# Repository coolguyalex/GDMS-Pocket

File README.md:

# GDMS:Pocket
**Goblinoid Dungeon Mastering System** — microcontroller-based handheld random table roller for tabletop RPGs.

---

## Concept

A dungeon master's companion designed to stay out of the way until you need it. Pull it out, roll a name, an encounter, a room, or whatever your table demands, then put it back in your pocket. GDMS:Pocket is designed to be as ignorable as it is useful — no app, no screen glare, no dead battery notification from your phone mid-session.

Content lives on a microSD card as plain CSV files and JSON recipe files. Adding, removing, or editing tables requires nothing more than a computer and a text editor.

---

## Current Firmware: Alpha 10 

### Implemented Features

- Navigate categories corresponding to folders on the SD card
- Browse and select CSV tables or JSON recipe generators within each category
- Roll a random result with a single button press; re-roll instantly with the same button
- Scroll long results that exceed the screen height
- Hold UP/DOWN for fast scrolling through lists
- LED breathing animation indicates power-on state
- LED "pop" flash on every button press
- Passive buzzer feedback — distinct tones per button
- Full options menu (A+B combo from any screen):
  - Buzzer on/off and volume (loud/soft)
  - LED on/off, pop on/off, brightness (low/med/high)
  - Breath speed (fast/med/slow)
  - Sleep timeout (5 min / 10 min / 30 min / never)
  - Data Edit Mode — exposes the SD card as a USB mass storage drive
- Settings persist to SD card (`/DATA/settings.cfg`) and reload on boot
- Sleep mode: display blanks after inactivity timeout; any button wakes it (suspended while in Data Edit Mode)
- Live battery voltage indicator in the header — 3-bar icon with critical flash
- Header titles truncated with `...` if they would overlap the battery icon
- Startup splash screen (2 seconds on boot)
- About screen with control reference

### Data Edit Mode

Selecting "Data Edit" from the options menu puts the device into USB mass storage mode: the SD card mounts on the connected computer as a normal removable drive, so content can be added, edited, or removed with a regular file explorer — no card removal required. The device still charges normally over the same USB-C connection while in this mode.

- Entered from the options menu (A → cycles into the mode)
- Screen displays "DATA EDIT MODE" / "press A + B to exit." while active
- Exit via A+B (held) — the same combo used elsewhere to open the options menu is repurposed here to exit, since the options menu isn't reachable while the SD card is handed off to the host
- On exit, the SD card is unmounted from the host, remounted for the firmware's own file access, and categories are rescanned so any added/removed/edited content shows up immediately
- Implemented via Adafruit_TinyUSB's mass storage (MSC) class, using the same SdFat `SD` object already used for file-level access elsewhere in the firmware — read/write/flush callbacks operate at the raw sector level rather than the file level
- Sleep timeout is disabled while in this mode so the screen doesn't blank mid-transfer

### JSON Recipe System (V1)

JSON files in a category folder act as multi-part generators. A recipe chains together rolls from multiple CSV tables and assembles them into a single composed output. Features include optional parts (probability `p`), repeat counts, cross-category table references, and a `format` string for custom output layouts. See **Content & Customisation** below and the recipe convention document in the repo for full details.

### CSV Weighted Tables

If a CSV file uses two columns — `weight,entry` — the first column is treated as an integer weight and results are sampled proportionally. Single-column CSVs treat all entries as equally likely. Lines beginning with `#` or `//` are treated as comments and skipped.

---

## Hardware

### Bill of Materials

| Component | Description |
|-----------|-------------|
| Adafruit Feather RP2040 Adalogger | MCU + built-in microSD slot |
| 1.5" SH1107 OLED (SPI, 128×128) | Display |
| 4× momentary pushbutton | Navigation (active-low) |
| Passive buzzer module (3-pin) | Audio feedback |
| LED + current-limiting resistor | Status indicator |
| 3.7V LiPo battery (JST connector) | Power |
| 2× 100kΩ resistor | Battery voltage divider |

### BOM with cost estimates
|Component                                |Price     |Source                                |
|-----------------------------------------|----------|--------------------------------------|
|Adafruit Feather RP2040 Adalogger        |$14.95    |Adafruit / DigiKey, retail single unit|
|1.5” SH1107 128×128 monochrome OLED (SPI)|$4.50     |AliExpress, bulk 10-pack pricing      |
|Momentary pushbuttons ×4                 |$0.60     |AliExpress, bulk 100pc pack           |
|Passive buzzer module                    |$0.35     |AliExpress, bulk pack                 |
|LED + resistor                           |$0.10     |AliExpress, bulk pack                 |
|3.7V LiPo battery w/ JST                 |$2.50     |AliExpress, bulk pack                 |
|100kΩ resistors ×2                       |$0.02     |AliExpress, bulk reel                 |
|Slide switch                             |$0.30     |AliExpress, bulk pack                 |
|Custom PCB, bare board (10-unit batch)   |$1.50     |PCBWay                                |
|3D printed PETG enclosure                |$3.00     |Self-sourced filament                 |
|Misc wire/headers/hardware               |$1.00     |AliExpress, bulk pack                 |
|**Total**                                |**$28.82**|                                      |

### Pin Mapping

#### OLED Display (SH1107, Software SPI)

| OLED Pin | Feather Pin |
|----------|-------------|
| VCC | 3V3 |
| GND | GND |
| SCL (CLK) | D13 |
| SDA (DATA) | D12 |
| DC | D11 |
| CS | D10 |
| RST | D9 |

> **Library patch required:** The U8g2 SH1107 128×128 driver sets `default_x_offset = 96` by default, which causes a 32px horizontal wrap on some panels. Set both `default_x_offset` and `flipmode_x_offset` to `0` in `u8x8_d_sh1107.c`. This must be re-applied after any U8g2 library update. See Log 8 for full details.
>
> This has recurred at least once in practice after installing an unrelated library (Adafruit TinyUSB) via Library Manager, which appears to have triggered a U8g2 reinstall/update as a side effect. Worth checking `default_x_offset`/`flipmode_x_offset` any time the display shows an unexplained horizontal shift, not just after deliberate U8g2 updates. As of U8g2's source (checked Feb 2025), the maintainer's own comment on this section confirms `0` is the correct value for panels like this one — see [olikraus/u8g2#2581](https://github.com/olikraus/u8g2/issues/2581).

#### Buttons (Active-Low, Internal Pull-Up)

| Button | Feather Pin |
|--------|-------------|
| UP | A1 |
| DOWN | A2 |
| A (select / roll) | A3 |
| B (back) | 24 |

Buttons are wired pin → GND. No external pull-up resistors needed.

#### Buzzer (Passive, PWM)

| Signal | Feather Pin |
|--------|-------------|
| SIG | D6 |
| VCC | 3V3 |
| GND | GND |

> A series resistor (~1kΩ) on the signal line is recommended to reduce volume to a comfortable level for table use.

#### LED

| Connection | Feather Pin |
|------------|-------------|
| Anode (via resistor) | D25 |
| Cathode | GND |

> Do not use `PIN_LED` as a variable name — it is defined as a macro in the RP2040 Arduino core.

#### Battery Voltage Divider

The Feather RP2040 Adalogger does not have a built-in battery monitor circuit. An external voltage divider must be wired as follows:

```
VBAT ──[ 100kΩ ]──┬──[ 100kΩ ]── GND
                  │
                  └── A0
```

| Signal | Feather Pin |
|--------|-------------|
| Divider center tap | A0 |

The firmware reads A0, multiplies by 2, and displays a 3-bar battery icon in the header. Voltage thresholds: FULL ≥4.0V, OK ≥3.7V, LOW ≥3.5V, CRIT <3.5V (flashing).

### SD Card

The Adalogger's built-in microSD slot is used via SdFat (Adafruit fork) on SPI1. Format the card as FAT32.

---

## SD Card Data Structure

```
/DATA/
  /category-name/
    table.csv
    generator.json
    _hidden-ingredient.csv
  /another-category/
    ...
  settings.cfg          ← written automatically by firmware
```

- `/DATA` is the root content directory. It must exist.
- Each immediate subfolder of `/DATA` becomes a navigable category in the UI.
- Folders nested deeper than one level are ignored.
- `.csv` and `.json` files within a category folder appear as selectable items.
- Files whose names begin with `_` are hidden from the UI but accessible to JSON recipes.
- `settings.cfg` is written automatically and should not be edited manually.

---

## Software

### Language & Framework

Arduino (C++) targeting the Adafruit Feather RP2040 Adalogger via the Arduino-Pico core.

### Library Dependencies

| Library | Purpose |
|---------|---------|
| U8g2 (olikraus) | OLED driver and graphics |
| SdFat – Adafruit Fork | microSD access |
| ArduinoJson | JSON recipe parsing |
| Adafruit TinyUSB | USB mass storage (Data Edit Mode) — requires Tools > USB Stack > Adafruit TinyUSB in Arduino IDE |

### Controls Reference

| Button | Category / File list | Table / Result view | Options menu | Data Edit Mode |
|--------|---------------------|---------------------|--------------|-----------------|
| UP | Scroll up | Scroll up | Previous option | — |
| DOWN | Scroll down | Scroll down | Next option | — |
| A | Select / enter | Re-roll | Cycle setting value | — |
| B | — (no-op at root) | Back to file list | Back | — |
| A + B (held) | Open options | Open options | — | Exit Data Edit Mode |

### Architecture Notes

- State machine with six modes: `MODE_CATS`, `MODE_FILES`, `MODE_TABLE`, `MODE_OPTIONS`, `MODE_ABOUT`, `MODE_DATA_EDIT`
- Page-buffer OLED rendering (`_1_` constructor) — redraws on input events only, with a periodic background refresh for animation (LED breath, battery icon flash)
- Non-blocking LED and buzzer using `millis()` timers throughout
- Battery sampled every 5 seconds via a non-blocking timer; 8-sample average
- All user settings persisted to `/DATA/settings.cfg` as key=value text immediately on change
- SD card is accessed two ways depending on mode: file-level (`SD.open()`, `FsFile`) for normal category/table browsing, and raw block/sector-level (`SD.card()->readSector()`/`writeSector()`) for Data Edit Mode's USB mass storage exposure — same underlying SdFat object, different API surface

---

## Planned / Future Features

- Auto-mode: a dearf-fortressian ambient atory generatir where randomyl generated entires drive a strange atory which unfolds before the reader. 
- Per-category icons (`_icon.bin`, 32×32 1-bit bitmap) rendered in the header
- Saved results — up to 10 entries written to SD, browsable on a Saved page
- Nested JSON recipes (recipes invoking other recipes)
- Ambient mode — auto-rolls at a set interval for generative table atmosphere
- Neopixel indicator
- Battery voltage shown in the About screen
- Migration from `StaticJsonDocument` to `JsonDocument` (ArduinoJson v7 alignment)
- **GDMS-pocket Companion App** — desktop tool for content authoring, generation, and firmware flashing (see below)

---

## GDMS-pocket Companion App (Planned)

A desktop companion tool for authoring and managing GDMS:Pocket content, shipped alongside the device rather than as a separate purchase. Not yet implemented — this section documents the intended design and open questions.

### Concept

**Data Edit Mode is now implemented on-device** (see Current Firmware above) — the SD card can be exposed as a plain USB mass storage drive from the options menu, no companion app required. The companion app remains planned as a richer, GDMS-aware layer on top of this: same name family, same visual language, same spirit of staying out of the way until needed, but with content-authoring tools (Markov-chain generation, structured CSV/JSON editing, firmware flashing) that a generic file explorer can't offer.

### Aesthetic

Black-on-green CLI-style interface, matching the terminal look of the original [GDMS](https://github.com/coolguyalex/GDMS) desktop tool. Navigation is entirely text-based:
- Keyboard shortcuts for every applet/action
- Clickable text labels as the mouse-driven alternative — text glows on hover and blinks briefly when clicked, echoing a terminal cursor rather than a conventional button

### Device Detection & Interaction

Still an open design question — rough intent:
- When the app is running and a GDMS:Pocket is connected via USB, the device should detect the companion app's presence (likely via a simple serial handshake) and unlock companion-aware functionality on-device, going beyond the generic mass-storage exposure Data Edit Mode already provides.
- Once connected, the app could:
  - Browse and directly edit category folders, CSV tables, and JSON recipes on the SD card
  - Generate new content — e.g. Markov-chain-based text generators trained on existing tables, to bootstrap new CSV entries from a sample of existing ones
  - Flash new firmware to the device (bundling firmware updates with the same tool used for content, instead of requiring separate Arduino IDE / bootloader steps)
  - **Chiptune mode** (low priority / just for fun) — compose or import chiptune-style songs and play them back through the device's passive buzzer, in the spirit of [goblinoidDungeonSynthSystem](https://github.com/coolguyalex/goblinoidDungeonSynthSystem)

### Open Questions

- ~~Whether "Data Edit Mode" on the device becomes a distinct on-device mode of its own, or stays implicit~~ — resolved: it's a distinct on-device mode, entered/exited explicitly from the options menu, and works as plain mass storage independent of any companion app
- Whether the companion app's smarter feature set (content generation, firmware flashing) talks to the device over serial while Data Edit Mode's plain mass-storage exposure remains the fallback for basic editing
- How much of the companion-aware logic should live in GDMS:Pocket firmware itself (e.g. a lightweight serial command protocol) vs. entirely in the companion app

---

## Changelog

| Version | Summary |
|---------|---------|
| Alpha 10| Data Edit Mode (USB mass storage for SD card content editing) |
| Alpha 9 | Battery voltage icon in header, header truncation, stale pin comment fixed |
| Alpha 8 | Scrollbar on category list, additional LED options |
| Alpha 7 | Sleep/wake, scrollbar in table view, About screen in options |
| Alpha 6 | A+B combo options menu |
| Alpha 5 | LED breathing and pop animations |
| Alpha 4 | List scrolling |
| Alpha 3 | Hold-to-scroll on UP/DOWN |
| Alpha 2 | Word-aware line wrapping |
| Alpha 1 | Initial SH1107 bring-up, pin map, full hardware test |

---

*GDMS:Pocket by Alexander Sousa, 2026*

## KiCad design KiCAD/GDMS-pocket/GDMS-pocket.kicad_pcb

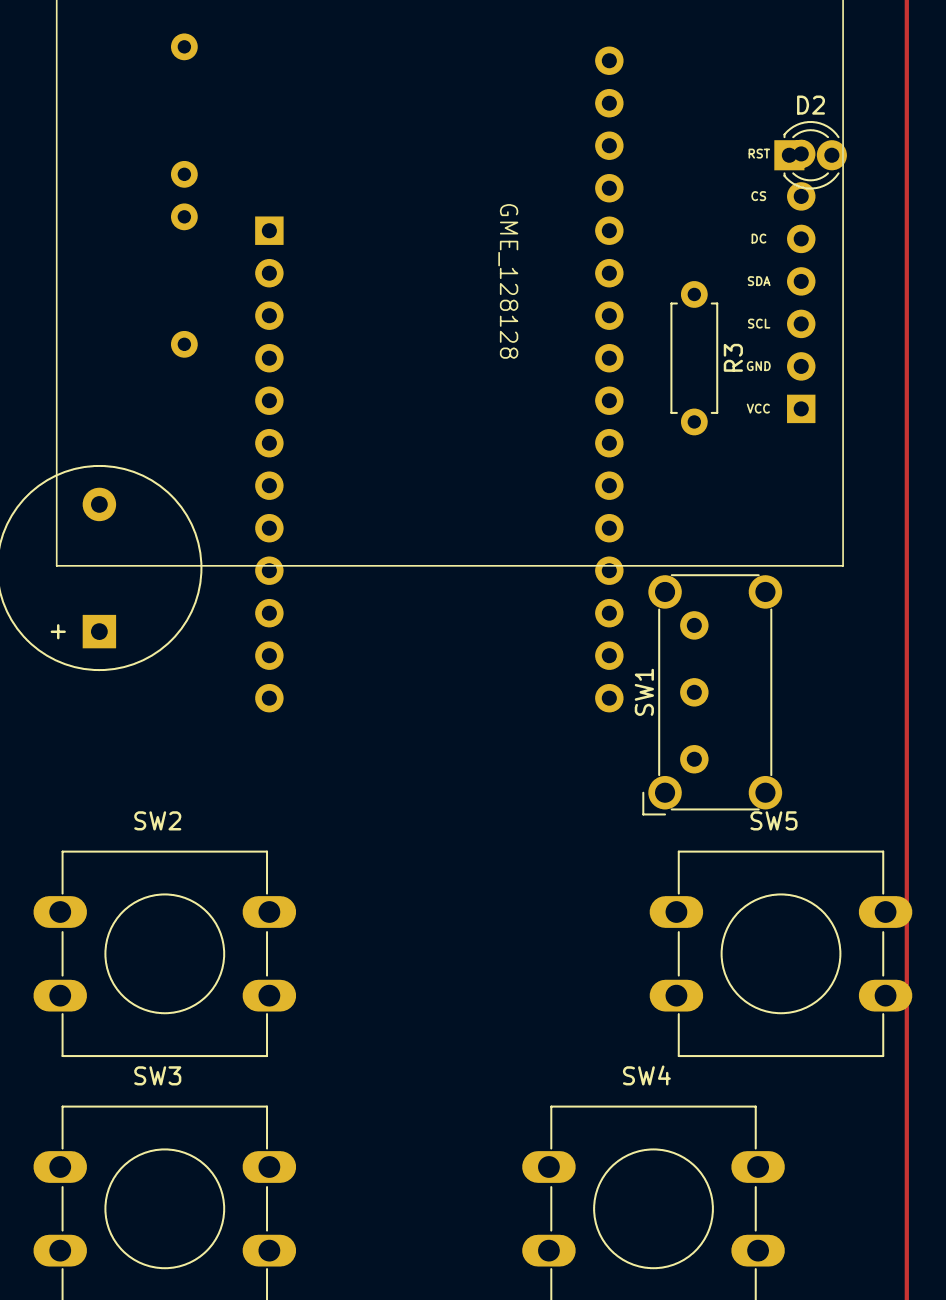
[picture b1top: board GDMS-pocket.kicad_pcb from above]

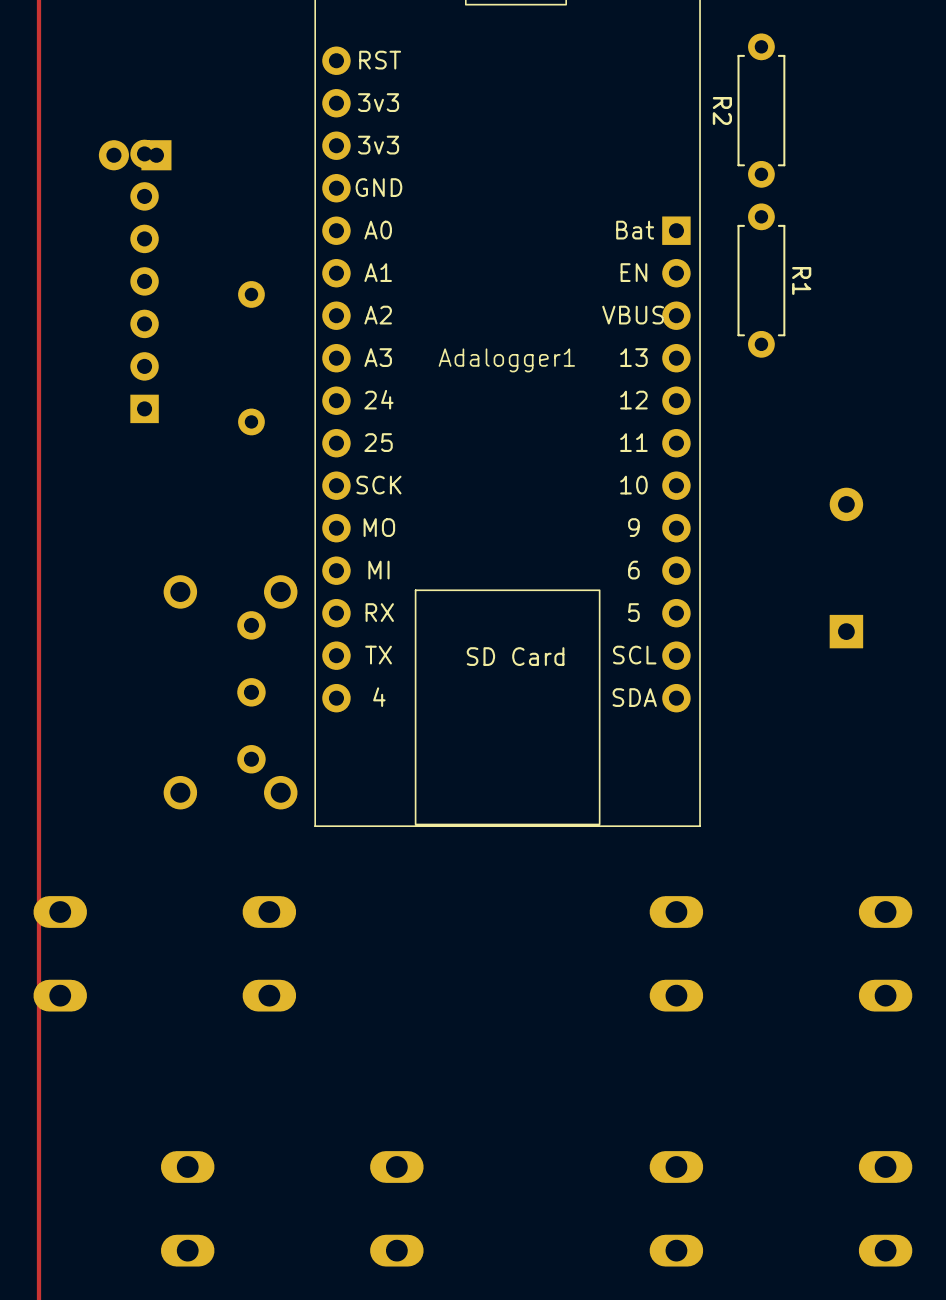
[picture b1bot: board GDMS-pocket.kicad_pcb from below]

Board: 2 copper layers, 12 parts (3 on the bottom side), 17 nets, no tracks yet.

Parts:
Adalogger1: Adafruit Feather Adalogger RP2040; Adafruit_Feather_Adalogger_RP2040
BZ1: Buzzer; Buzzer_12x9.5RM7.6
D2: LED; LED_D3.0mm
GME_128128: SH1107; 128128_SPI_SH1107
R1, R2: 100k; R_Axial_DIN0207_L6.3mm_D2.5mm_P7.62mm_Horizontal
R3: 1k; R_Axial_DIN0207_L6.3mm_D2.5mm_P7.62mm_Horizontal
SW1: SW_SPDT; SW_E-Switch_EG1224_SPDT_Angled
SW2, SW3, SW4, SW5: SW_Push; SW_PUSH-12mm

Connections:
+3V3: Adalogger1.27 (3v3), GME_128128.1 (VCC)
GND: Adalogger1.25 (GND/GND), BZ1.2 (-), D2.1 (K), GME_128128.2 (GND), R2.1, SW1.3 (C), SW2.2, SW3.2, SW4.2, SW5.2
unnamed: Adalogger1.24 (A0/GPIO26), R1.1, R2.2
unnamed: Adalogger1.23 (A1/GPIO27), SW3.1
unnamed: Adalogger1.22 (A2/GPIO28), SW2.1
unnamed: Adalogger1.21 (A3/GPIO29), SW5.1
unnamed: Adalogger1.4 (D6/GPIO6), R3.1
unnamed: Adalogger1.5 (D9/GPIO9), GME_128128.7 (RST)
unnamed: Adalogger1.6 (D10/GPIO10), GME_128128.6 (CS)
unnamed: Adalogger1.7 (D11/GPIO11), GME_128128.5 (DC)
unnamed: Adalogger1.8 (D12/GPIO12), GME_128128.4 (SDA)
unnamed: Adalogger1.9 (D13/GPIO13), GME_128128.3 (SCL)
unnamed: Adalogger1.20 (D24/GPIO24), SW4.1
unnamed: Adalogger1.19 (D25/GPIO25), BZ1.1 (+)
unnamed: Adalogger1.11 (EN), SW1.2 (B)
unnamed: Adalogger1.12 (VBAT), R1.2
unnamed: D2.2 (A), R3.2

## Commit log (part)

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2025-12-25 adding data files
2025-12-25 upload more data and resructure
2025-12-25 new files and rearranged structure
2025-12-25 dice data
2025-12-25 rename and file extension changes
2025-12-26 update files
2025-12-26 file tree screenshot
2025-12-26 file structure
2025-12-26 comment
2025-12-26 changeing files
2025-12-26 reupload
2025-12-26 more readme and file names
2025-12-26 restructure
2025-12-27 updated logs
2025-12-27 stuff
2025-12-27 fixed inaccurate V02 code
2025-12-27 new LED features
    breathing and pop on press
2025-12-28 move sketch
2025-12-28 mini-dice roller for arduino nano
    Sketch design for the nano paying heed to limitted storage and RAM
2025-12-29 writing for arduino nano
    Much code writen for the arduino nano such that an external SD module is not needed. Spartan UI redesign, and other flash memeory and RAM saving measures taken. No SD card means all lists for random 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
    Log updated to reflect changes.
2025-12-29 Rename files, add MCU comparison
2025-12-29 blueprint
2025-12-29 creating tiny-dungeon
2025-12-29 change file ext.
2026-01-02 beginning CircuitPython
2026-01-03 libraries
2026-01-03 example python stuff
2026-01-04 Revise README for GDMS:Pocket with new features
    Updated the README with new features, hardware details, and functionality for GDMS:Pocket.
2026-01-04 MCU boards comparisons
2026-01-04 editting readme to reflect wiring changes
2026-01-04 rearrangign files and folders. adding some test code for V4
2026-01-04 bunch of stuff
2026-01-04 addded a little helper script for batchquoting
2026-01-04 reached POC v1
2026-01-04 final sketch for the night, updated logs, juggled files
2026-01-04 deleted duplicate files
2026-01-06 deleted corrupted version of POC_4
    deleted corrupted version of POC_4 and changed
    #include "SdFat.h"
    to
    #include <SdFat.h>
2026-01-06 Implement SD config file and rearrange files
    Implement SD config file
    rearrange files
    creating plaintext duplicates of code.
2026-01-06 A and B button flip
2026-01-07 Seem to have implemented Adafruit-fork-free SD reading.
2026-01-07 Implemented JSON recipe v1
    JSON Recipe System – V1 Summary
    What V1 Accomplishes
    V1 introduces JSON-based generators (“recipes”) that behave exactly like CSV tables from the user’s point of view, while allowing internally chained rolls.
    Key capabilities:
    JSON recipes appear in the UI alongside CSV tables
    .json files are listed and selectable just like .csv
2026-01-07 Updated to remove deprecated functions
    deprecated arduino Json functions (dynamic vs static) eliminate din favor of newer functions.
2026-01-08 Create delete.txt.
2026-01-08 monster table uploads
2026-01-10 Add OLED test sketch for RP2040 using U8g2 library
2026-01-10 Rename OLED test file to correct format
2026-01-10 Rename delete.txt. to delete.txt
2026-01-10 Revise README for clarity and additional details
    Updated README to enhance clarity and structure, including hardware pin plan, library table, and functional specifications.
2026-01-10 Revise README with project overview and hardware info
    Updated README.md with new project details and hardware specifications.
2026-01-11 Revise README with hardware and software updates
    Updated README to include new hardware details and functionality.
2026-01-11 Revise README for improved structure and content
    Updated README.md to enhance clarity and add details.
2026-01-11 Add dev log for SH1107 OLED bring-up and validation
    Documented the bring-up process and issues encountered with the SH1107 OLED display on the Feather RP2040 Adalogger.
2026-01-11 Rename Log 7 260103 GDMS_Pocket_POC_V03.md to Log7 260103 GDMS_Pocket_POC_V03.md
2026-01-11 better test which includes all components - and renamed
    sketch tests 1.5" 128 x 128 OLED, 4 buttons, passive buzzer, and LED.
2026-01-11 Added JSON Recipes, and SplashScreen
2026-01-11 Enhance development log with JSON recipe details
    Updated the development log to include JSON recipe functions and file ignore behavior.
2026-01-11 Rearranged files
2026-01-11 POC_V06 is focused on correct path handling for data files within the context of Json recipes.
2026-01-11 editting data files.
2026-01-11 added class.csv for PC generation
2026-01-11 adding weights to CSV files. correcting to eliminate "," or blank gnerations. Created feature summary / changelog
2026-01-11 -added code to sort category entries by extension (JSON firtst).
    -Added a JSON recipe for monster generation
    -split multi-column csv's into seperate files
2026-01-12 Restructuring file system
2026-01-14 Dice and potion csvs added
2026-01-14 Added aspirational jsons
2026-01-14 rearranged rows for test
2026-01-14 added JSON functionality to repeatedly sample csv files and concatenate generated data. Concatenation can be via commas or newlines.
2026-01-14 changed file extensions and eliminated duplicate files.
2026-01-14 editted JSON recipes and CSV titles. Rewrote JASON handler to actually generate repeat rolls.
2026-01-14 eddited recipes and CSVs
2026-01-14 reupload last good code
2026-01-14 Alpha Created
2026-01-14 editted JSON
2026-01-16 rename alpha branch
2026-01-19 battery meter test sketch and file renaming
2026-01-19 changed file stucture for organizaiton
2026-01-25 creating some KiCAD files for PCB design
2026-01-26 uploading schematic data in KiCAD and manufacturer data on 1.5" OLED SPI display
2026-02-04 Uploading KiCad Files
2026-02-05 removing KiCad files
2026-02-17 arduino shenanegins
2026-02-28 fixed data files, added new files and json recipes,
2026-02-28 new battery indicator sketch
2026-02-28 altered log. and GDMSpAlpha code to incorporate beginning of Settings menu for buzzer and other downstream options.
2026-02-28 roll back changes manually via ctrl+z and updated code to match real button pins.
2026-03-05 gettgin started guide, devlog, most recent code for Alpha
